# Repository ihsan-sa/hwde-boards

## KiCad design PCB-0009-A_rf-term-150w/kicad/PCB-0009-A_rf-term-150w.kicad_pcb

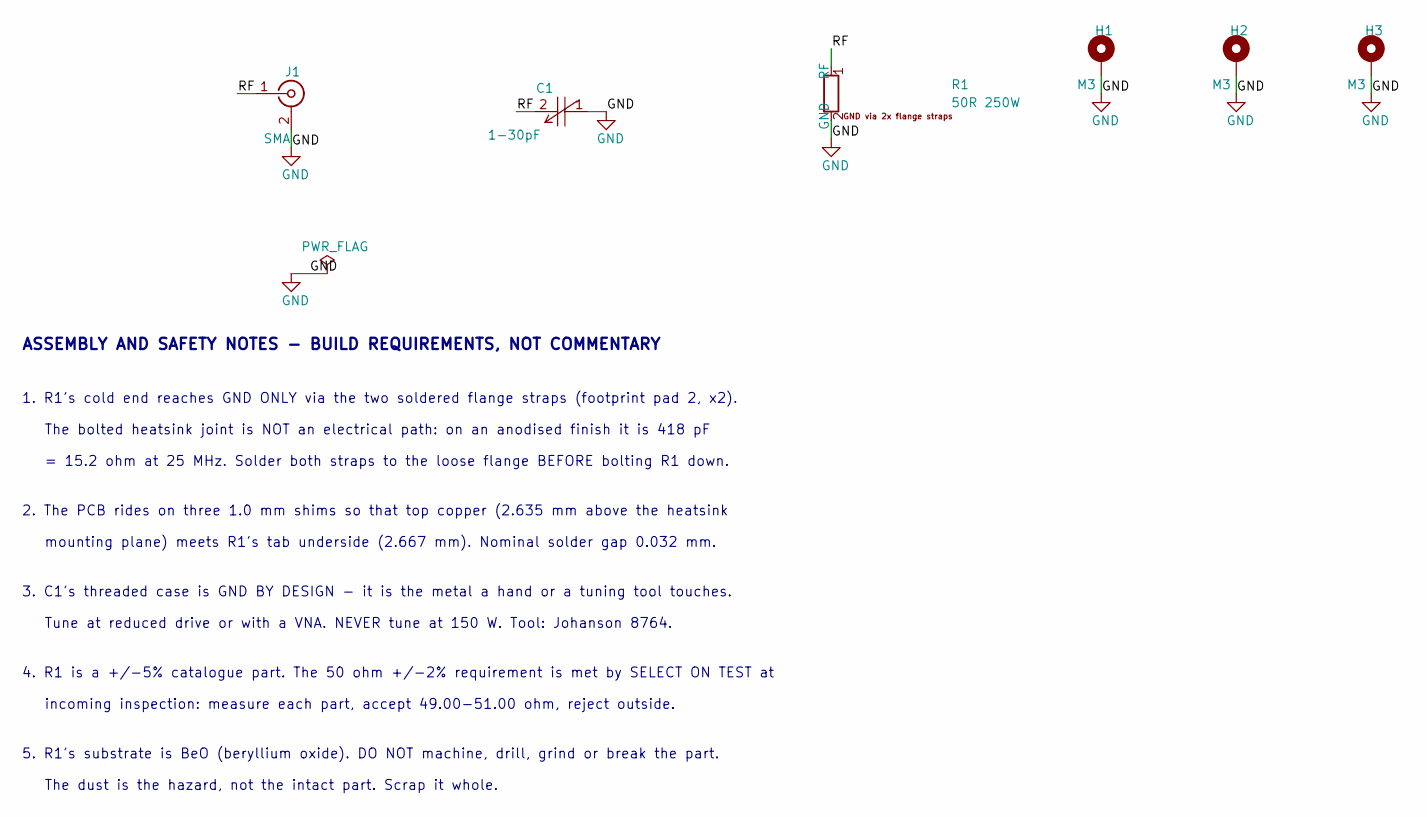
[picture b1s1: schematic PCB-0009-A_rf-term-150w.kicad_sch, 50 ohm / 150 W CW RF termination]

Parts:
C1: 1-30pF; CAP-ADJ-TH_2P-BD7.5_5602; MPN 5602; DigiKey 1956-1000-ND
H1, H2, H3: M3; MountingHole_3.2mm_M3_Pad_5.0mm
J1: SMA; SMA_BAT_Wireless_BWSMA-KWE-Z001; MPN SMA-KWE; LCSC C7498154
R1: 50R 250W; R_LapPad_T50R0-250-12X; MPN T50R0-250-12X; DigiKey 4353-T50R0-250-12X-ND

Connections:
/RF: C1.2 (ROTOR), J1.1 (In), R1.1 (RF)
GND: C1.1 (STATOR), H1.1, H2.1, H3.1, J1.2 (Ext), R1.2 (GND)

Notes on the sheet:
ASSEMBLY AND SAFETY NOTES - BUILD REQUIREMENTS, NOT COMMENTARY
1. R1's cold end reaches GND ONLY via the two soldered flange straps (footprint pad 2, x2).
The bolted heatsink joint is NOT an electrical path: on an anodised finish it is 418 pF
= 15.2 ohm at 25 MHz. Solder both straps to the loose flange BEFORE bolting R1 down.
2. The PCB rides on three 1.0 mm shims so that top copper (2.635 mm above the heatsink
mounting plane) meets R1's tab underside (2.667 mm). Nominal solder gap 0.032 mm.
3. C1's threaded case is GND BY DESIGN - it is the metal a hand or a tuning tool touches.
Tune at reduced drive or with a VNA. NEVER tune at 150 W. Tool: Johanson 8764.
4. R1 is a +/-5% catalogue part. The 50 ohm +/-2% requirement is met by SELECT ON TEST at
incoming inspection: measure each part, accept 49.00-51.00 ohm, reject outside.
5. R1's substrate is BeO (beryllium oxide). DO NOT machine, drill, grind or break the part.
The dust is the hazard, not the intact part. Scrap it whole.

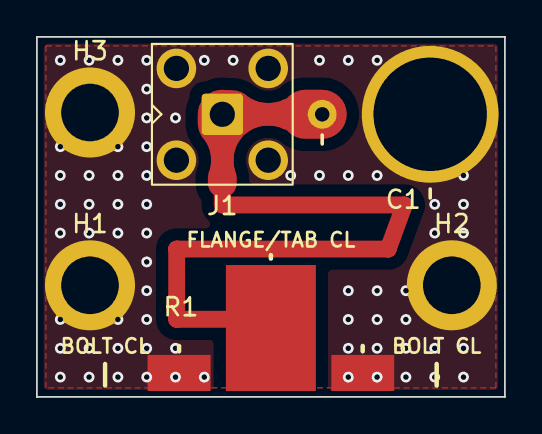
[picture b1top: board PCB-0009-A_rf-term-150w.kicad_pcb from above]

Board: 2 copper layers, 26.0 x 20.0 mm, 6 parts (0 on the bottom side), 2 nets.

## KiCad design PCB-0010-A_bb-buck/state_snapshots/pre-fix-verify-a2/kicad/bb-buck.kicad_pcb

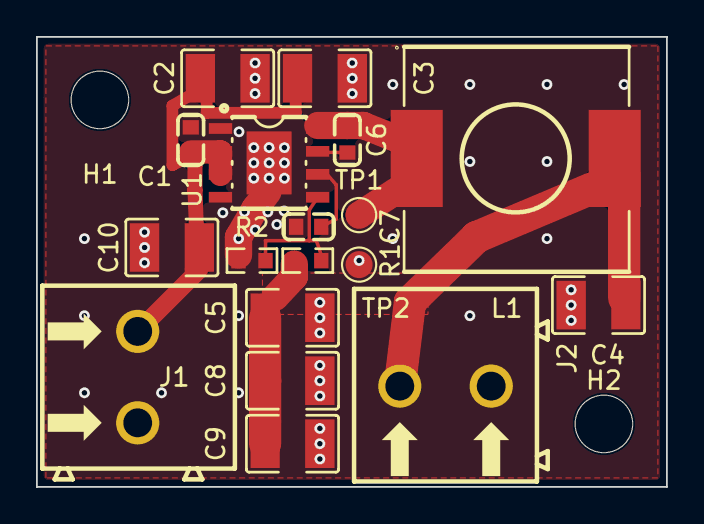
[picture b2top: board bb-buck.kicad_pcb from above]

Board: 2 copper layers, 35.0 x 25.0 mm, 20 parts (0 on the bottom side), 7 nets.

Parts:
C1: 220nF 50V X7R; C0603
C2, C3, C10: 10uF 50V X7R; C1210
C4, C5, C8, C9: 22uF 25V X7R; C1210
C6: 100nF 50V X7R; C0603
C7: 1uF 25V X7R; C0603
H1, H2: M3_3.2mm; MountingHole_3.2mm_M3
J1, J2: KF128-5.08-2P; CONN-TH_P5.08_KF128-5.08-2P
L1: 15uH; IND-SMD_L12.5-W12.5_RLF12545T
R1: 102k 0.1% 25ppm; R0603
R2: 25.5k 0.1% 25ppm; R0603
TP1: SW; TestPoint_Pad_D1.5mm
TP2: GND; TestPoint_Pad_D1.5mm
U1: LMR33630ADDAR; ESOP-8_L4.9-W3.9-P1.27-LS6.0-TL-EP

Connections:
+5V: C4.1, C5.1, C8.1, C9.1, J2.1, L1.2, R1.1
+VIN: C1.1, C2.1, C3.1, C10.1, J1.1, U1.2, U1.3
/BST: C6.1, U1.7
/FB: R1.2, R2.1, U1.5
/SW: C6.2, L1.1, TP1.1, U1.8
/VCC: C7.1, U1.6
GND: C1.2, C2.2, C3.2, C4.2, C5.2, C7.2, C8.2, C9.2, C10.2, J1.2, J2.2, R2.2, TP2.1, U1.1, U1.9

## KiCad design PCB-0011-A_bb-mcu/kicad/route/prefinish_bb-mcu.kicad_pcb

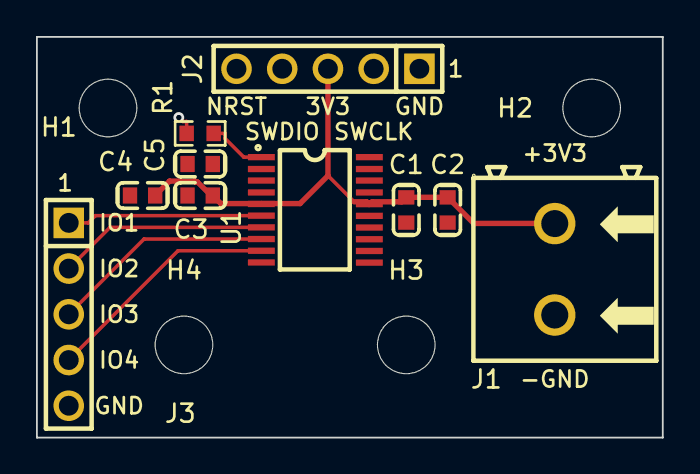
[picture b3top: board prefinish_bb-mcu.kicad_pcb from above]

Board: 2 copper layers, 34.8 x 22.3 mm, 14 parts (0 on the bottom side), 10 nets.

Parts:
C1, C5: 100nF 50V X7R; C0603
C2: 4.7uF 16V X7R; C0603
C3: 10nF 25V X7R; C0603
C4: 1uF 16V X7R; C0603
H1, H2, H3, H4: MountingHole_3.2mm_M3
J1: 2P 5.08mm screw terminal THT; CONN-TH_2P-P5.00_WJ500V-5.08-2P
J2, J3: 1x5 2.54mm male THT; HDR-TH_5P-P2.54-V-M
R1: 10k; R0603
U1: STM32F030F4P6TR; SOP-20_L6.5-W4.4-P0.65-LS6.4-BL

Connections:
+3V3: C1.1, C2.1, C3.1, C4.1, J1.1, J2.3, U1.5, U1.16
/BOOT0: R1.1, U1.1
/IO1: J3.1, U1.6
/IO2: J3.2, U1.7
/IO3: J3.3, U1.8
/IO4: J3.4, U1.9
/NRST: C5.1, J2.5, U1.4
/SWCLK: J2.2, U1.20
/SWDIO: J2.4, U1.19
GND: C1.2, C2.2, C3.2, C4.2, C5.2, J1.2, J2.1, J3.5, R1.2, U1.15

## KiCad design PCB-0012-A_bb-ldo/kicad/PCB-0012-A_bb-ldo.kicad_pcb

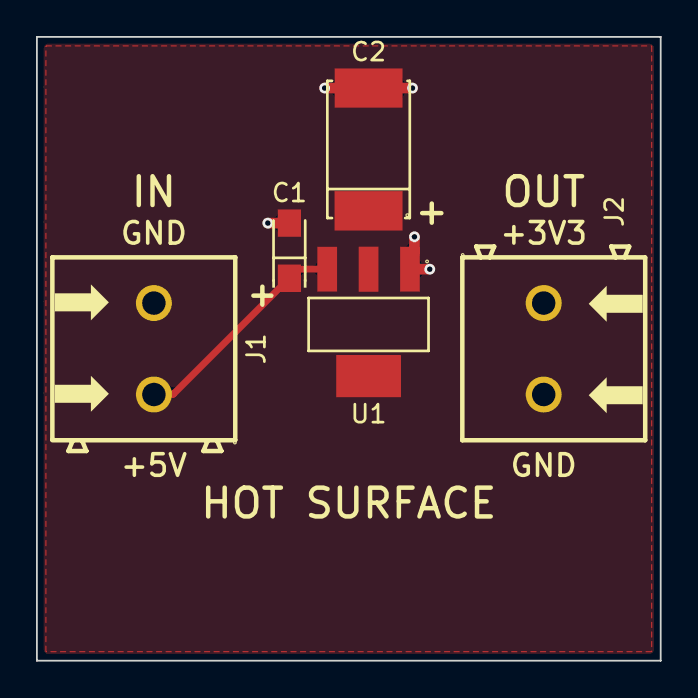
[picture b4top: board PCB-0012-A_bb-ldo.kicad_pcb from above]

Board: 2 copper layers, 34.7 x 34.7 mm, 5 parts (0 on the bottom side), 3 nets.

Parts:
C1: 10uF 16V solid tantalum; CAP-SMD_L3.2-W1.6-RD-C7171
C2: 22uF 16V solid tantalum ESR 0.8ohm; CAP-SMD_L7.3-W4.3
J1, J2: 2P 5.08mm THT screw terminal; CONN-TH_2P-P5.00_WJ500V-5.08-2P
U1: AMS1117-3.3; SOT-223-3_L6.5-W3.4-P2.30-LS7.0-BR

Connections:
+3V3: C2.1, J2.1, U1.2, U1.4
+5V: C1.1, J1.1, U1.3
GND: C1.2, C2.2, J1.2, J2.2, U1.1
